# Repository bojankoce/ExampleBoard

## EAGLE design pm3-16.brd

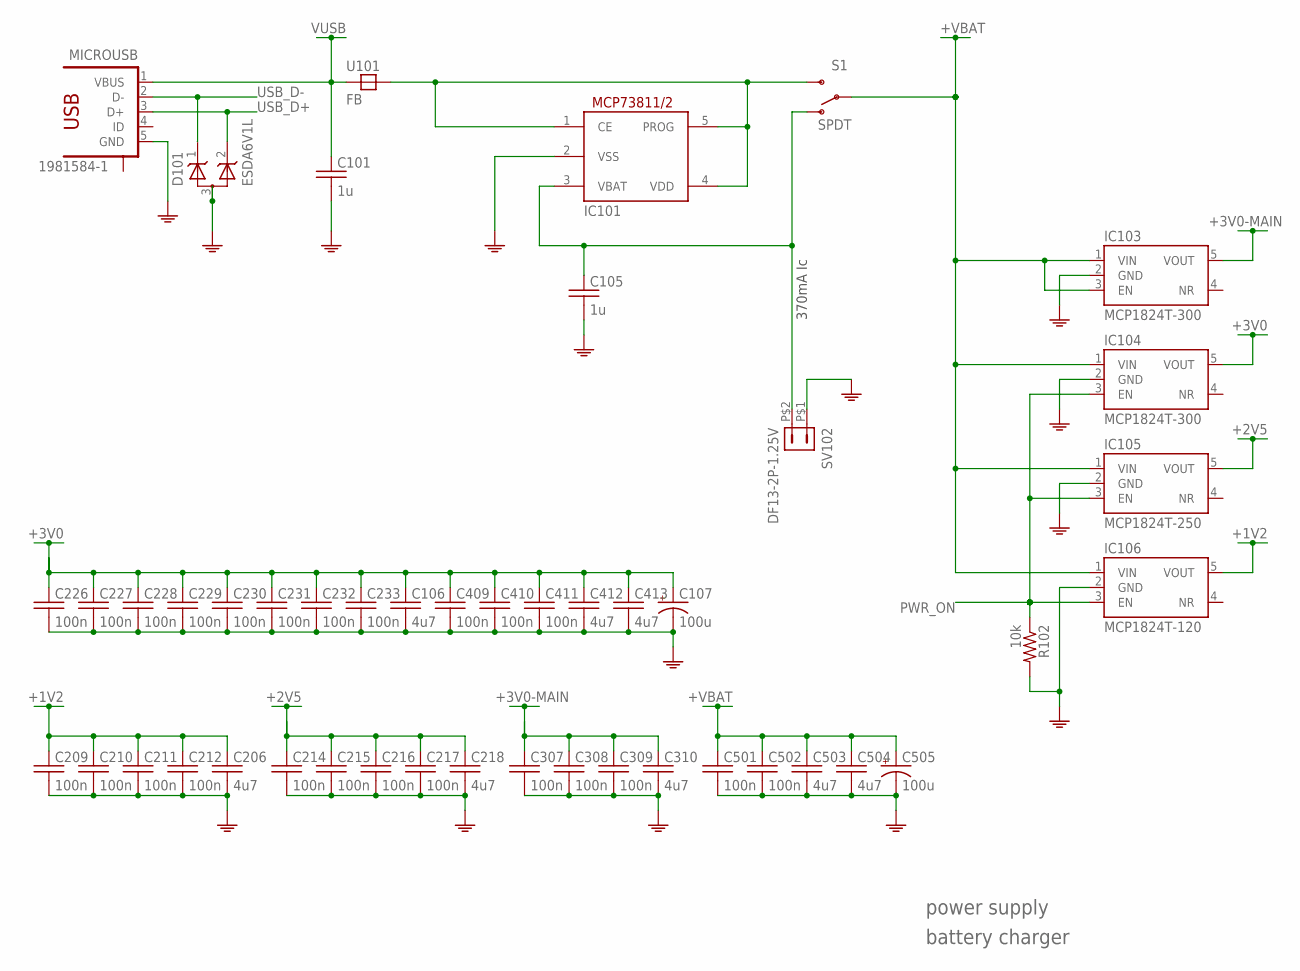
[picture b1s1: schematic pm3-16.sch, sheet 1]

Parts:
C101, C105: 1u; 0603
C106, C206, C218, C310, C412, C413, C503, C504: 4u7; 0603
C107, C505: 100u; 153CLV-0605
C209, C210, C211, C212, C214, C215, C216, C217, C226, C227, C228, C229, C230, C231, C232, C233, C307, C308, C309, C409, C410, C411, C501, C502: 100n; 0603
D101: ESDA6V1L; SOT-23-3
IC101: MCP73811/2; SOT23-5L
IC103, IC104: MCP1824T-300; SOT-23-5
IC105: MCP1824T-250; SOT-23-5
IC106: MCP1824T-120; SOT-23-5
MICROUSB: 1981584-1
R102: 10k; 0603
S1: SPDT; SWITCH-SPDT-SMD
SV102: DF13-2P-1.25V; DF13C-2P-1.25V
U101: FB; 0805

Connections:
+1V2: C206.1, C209.1, C210.1, C211.1, C212.1, IC106.5 (VOUT); also elsewhere on the board
+2V5: C214.1, C215.1, C216.1, C217.1, C218.1, IC105.5 (VOUT); also elsewhere on the board
+3V0: C106.1, C107.+, C226.1, C227.1, C228.1, C229.1, C230.1, C231.1, C232.1, C233.1, C409.1, C410.1, C411.1, C412.1, C413.1, IC104.5 (VOUT); also elsewhere on the board
+3V0-MAIN: C307.1, C308.1, C309.1, C310.1, IC103.5 (VOUT); also elsewhere on the board
+VBAT: C501.1, C502.1, C503.1, C504.1, C505.+, IC103.1 (VIN), IC103.3 (EN), IC104.1 (VIN), IC105.1 (VIN), IC106.1 (VIN), S1.2; also elsewhere on the board
BAT: C105.1, IC101.3 (VBAT), S1.1 (O), SV102.P$2 (2)
GND: C101.2, C105.2, C106.2, C107.-, C206.2, C209.2, C210.2, C211.2, C212.2, C214.2, C215.2, C216.2, C217.2, C218.2, C226.2, C227.2, C228.2, C229.2, C230.2, C231.2, C232.2, C233.2, C307.2, C308.2, C309.2, C310.2, C409.2, C410.2, C411.2, C412.2, C413.2, C501.2, C502.2, C503.2, C504.2, C505.-, D101.3 (AA), IC101.2 (VSS), IC103.2 (GND), IC104.2 (GND), IC105.2 (GND), IC106.2 (GND), MICROUSB.5 (GND), R102.2, SV102.P$1 (1); also elsewhere on the board
unnamed: IC101.1 (CE), IC101.4 (VDD), IC101.5 (PROG), S1.3 (S), U101.2 (B)
PWR_ON: IC104.3 (EN), IC105.3 (EN), IC106.3 (EN), R102.1; also elsewhere on the board
USB_D+: D101.2 (K2), MICROUSB.3 (D+); also elsewhere on the board
USB_D-: D101.1 (K1), MICROUSB.2 (D-); also elsewhere on the board
VUSB: C101.1, MICROUSB.1 (VBUS), U101.1 (A)

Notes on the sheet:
power supply
battery charger
370mA Ic

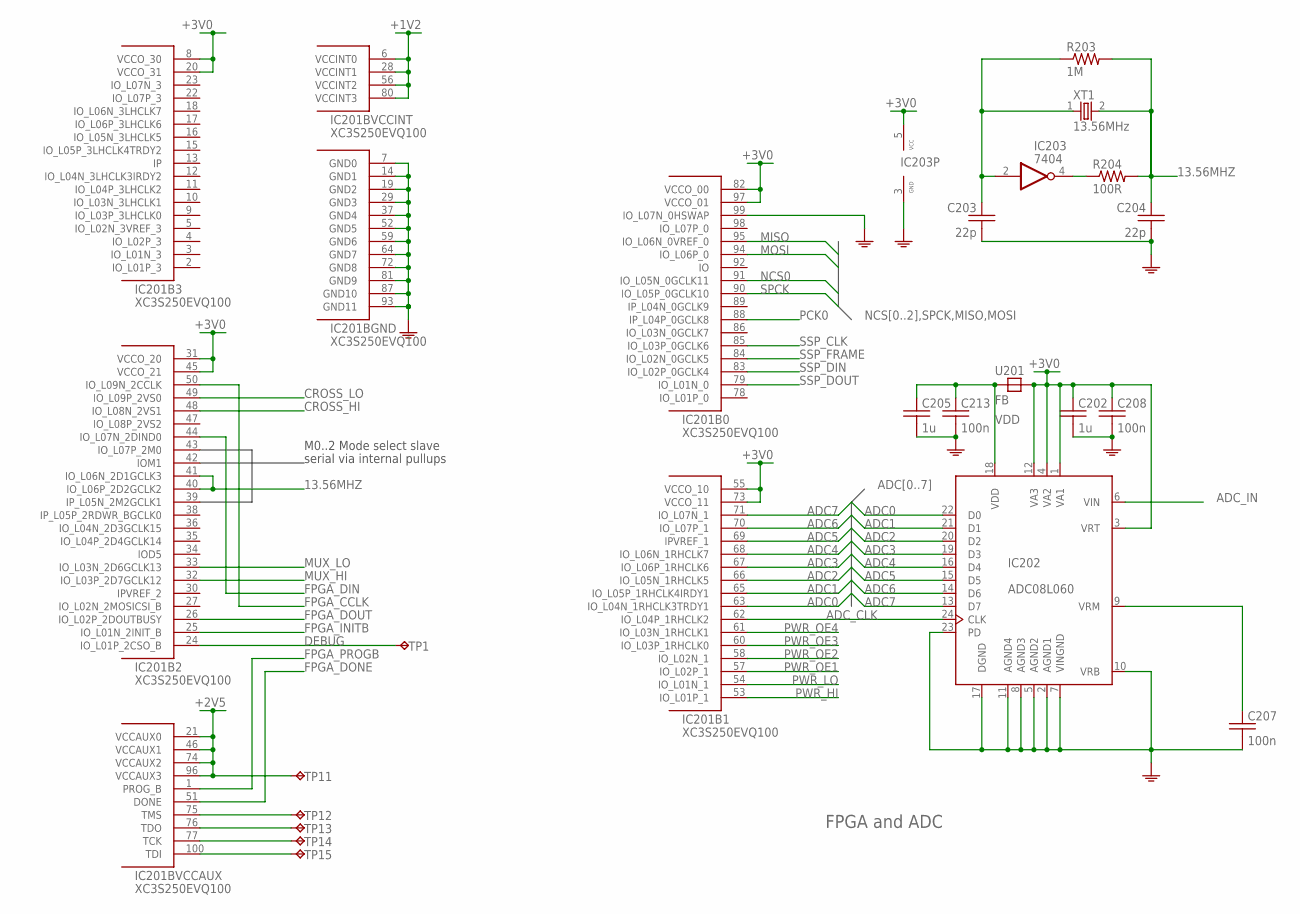
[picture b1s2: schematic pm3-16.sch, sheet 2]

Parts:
C202, C205: 1u; 0603
C203, C204: 22p; 0603
C207, C208, C213: 100n; 0603
IC201: XC3S250EVQ100; VQ100
IC202: ADC08L060; TSSOP24
IC203: 7404; SOT-23-5
R203: 1M; 0603
R204: 100R; 0603
TP1, TP11, TP12, TP13, TP14, TP15: TPTP06SQ; TP06SQ
U201: FB; 0805
XT1: 13.56MHz; 6035

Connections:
13.56MHZ: C204.1, IC201.40 (IO_L06P_2D2GCLK2), IC201.41 (IO_L06N_2D1GCLK3), R203.2, R204.2, XT1.2
+1V2: IC201.6 (VCCINT0), IC201.28 (VCCINT1), IC201.56 (VCCINT2), IC201.80 (VCCINT3); also elsewhere on the board
+2V5: IC201.21 (VCCAUX0), IC201.46 (VCCAUX1), IC201.74 (VCCAUX2), IC201.96 (VCCAUX3), TP11.TP; also elsewhere on the board
+3V0: C202.1, C208.1, IC201.8 (VCCO_30), IC201.20 (VCCO_31), IC201.31 (VCCO_20), IC201.45 (VCCO_21), IC201.55 (VCCO_10), IC201.73 (VCCO_11), IC201.82 (VCCO_00), IC201.97 (VCCO_01), IC202.1 (VA1), IC202.3 (VRT), IC202.4 (VA2), IC202.12 (VA3), IC203.5 (VCC), U201.2 (B); also elsewhere on the board
ADC0: IC201.63 (IO_L04N_1RHCLK3TRDY1), IC202.22 (D0)
ADC1: IC201.65 (IO_L05P_1RHCLK4IRDY1), IC202.21 (D1)
ADC2: IC201.66 (IO_L05N_1RHCLK5), IC202.20 (D2)
ADC3: IC201.67 (IO_L06P_1RHCLK6), IC202.19 (D3)
ADC4: IC201.68 (IO_L06N_1RHCLK7), IC202.16 (D4)
ADC5: IC201.69 (IPVREF_1), IC202.15 (D5)
ADC6: IC201.70 (IO_L07P_1), IC202.14 (D6)
ADC7: IC201.71 (IO_L07N_1), IC202.13 (D7)
ADC_CLK: IC201.62 (IO_L04P_1RHCLK2), IC202.24 (CLK)
ADC_IN: IC202.6 (VIN); also elsewhere on the board
CROSS_HI: IC201.48 (IO_L08N_2VS1); also elsewhere on the board
CROSS_LO: IC201.49 (IO_L09P_2VS0); also elsewhere on the board
DEBUG: IC201.24 (IO_L01P_2CSO_B), TP1.TP
FPGA_CCLK: IC201.50 (IO_L09N_2CCLK); also elsewhere on the board
FPGA_DIN: IC201.44 (IO_L07N_2DIND0); also elsewhere on the board
FPGA_DONE: IC201.51 (DONE); also elsewhere on the board
FPGA_DOUT: IC201.26 (IO_L02P_2DOUTBUSY); also elsewhere on the board
FPGA_INITB: IC201.25 (IO_L01N_2INIT_B); also elsewhere on the board
FPGA_PROGB: IC201.1 (PROG_B); also elsewhere on the board
FPGA_TCK: IC201.77 (TCK), TP14.TP
FPGA_TDI: IC201.100 (TDI), TP15.TP
FPGA_TDO: IC201.76 (TDO), TP13.TP
FPGA_TMS: IC201.75 (TMS), TP12.TP
GND: C202.2, C203.2, C204.2, C205.2, C207.2, C208.2, C213.2, IC201.7 (GND0), IC201.14 (GND1), IC201.19 (GND2), IC201.29 (GND3), IC201.37 (GND4), IC201.52 (GND5), IC201.59 (GND6), IC201.64 (GND7), IC201.72 (GND8), IC201.81 (GND9), IC201.87 (GND10), IC201.93 (GND11), IC201.99 (IO_L07N_0HSWAP), IC202.2 (AGND1), IC202.5 (AGND2), IC202.7 (VINGND), IC202.8 (AGND3), IC202.10 (VRB), IC202.11 (AGND4), IC202.17 (DGND), IC202.23 (PD), IC203.3 (GND); also elsewhere on the board
MISO: IC201.95 (IO_L06N_0VREF_0); also elsewhere on the board
MOSI: IC201.94 (IO_L06P_0); also elsewhere on the board
MUX_HI: IC201.32 (IO_L03P_2D7GCLK12); also elsewhere on the board
MUX_LO: IC201.33 (IO_L03N_2D6GCLK13); also elsewhere on the board
unnamed: C207.1, IC202.9 (VRM)
unnamed: IC203.4 (O), R204.1
unnamed: C203.1, IC203.2 (I), R203.1, XT1.1
NCS0: IC201.91 (IO_L05N_0GCLK11); also elsewhere on the board
PCK0: IC201.88 (IP_L04P_0GCLK8); also elsewhere on the board
PWR_HI: IC201.53 (IO_L01P_1); also elsewhere on the board
PWR_LO: IC201.54 (IO_L01N_1); also elsewhere on the board
PWR_OE1: IC201.57 (IO_L02P_1); also elsewhere on the board
PWR_OE2: IC201.58 (IO_L02N_1); also elsewhere on the board
PWR_OE3: IC201.60 (IO_L03P_1RHCLK0); also elsewhere on the board
PWR_OE4: IC201.61 (IO_L03N_1RHCLK1); also elsewhere on the board
SPCK: IC201.90 (IO_L05P_0GCLK10); also elsewhere on the board
SSP_CLK: IC201.85 (IO_L03P_0GCLK6); also elsewhere on the board
SSP_DIN: IC201.83 (IO_L02P_0GCLK4); also elsewhere on the board
SSP_DOUT: IC201.79 (IO_L01N_0); also elsewhere on the board
SSP_FRAME: IC201.84 (IO_L02N_0GCLK5); also elsewhere on the board
VDD: C205.1, C213.1, IC202.18 (VDD), U201.1 (A)

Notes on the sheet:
FPGA and ADC
M0..2 Mode select slave
serial via internal pullups

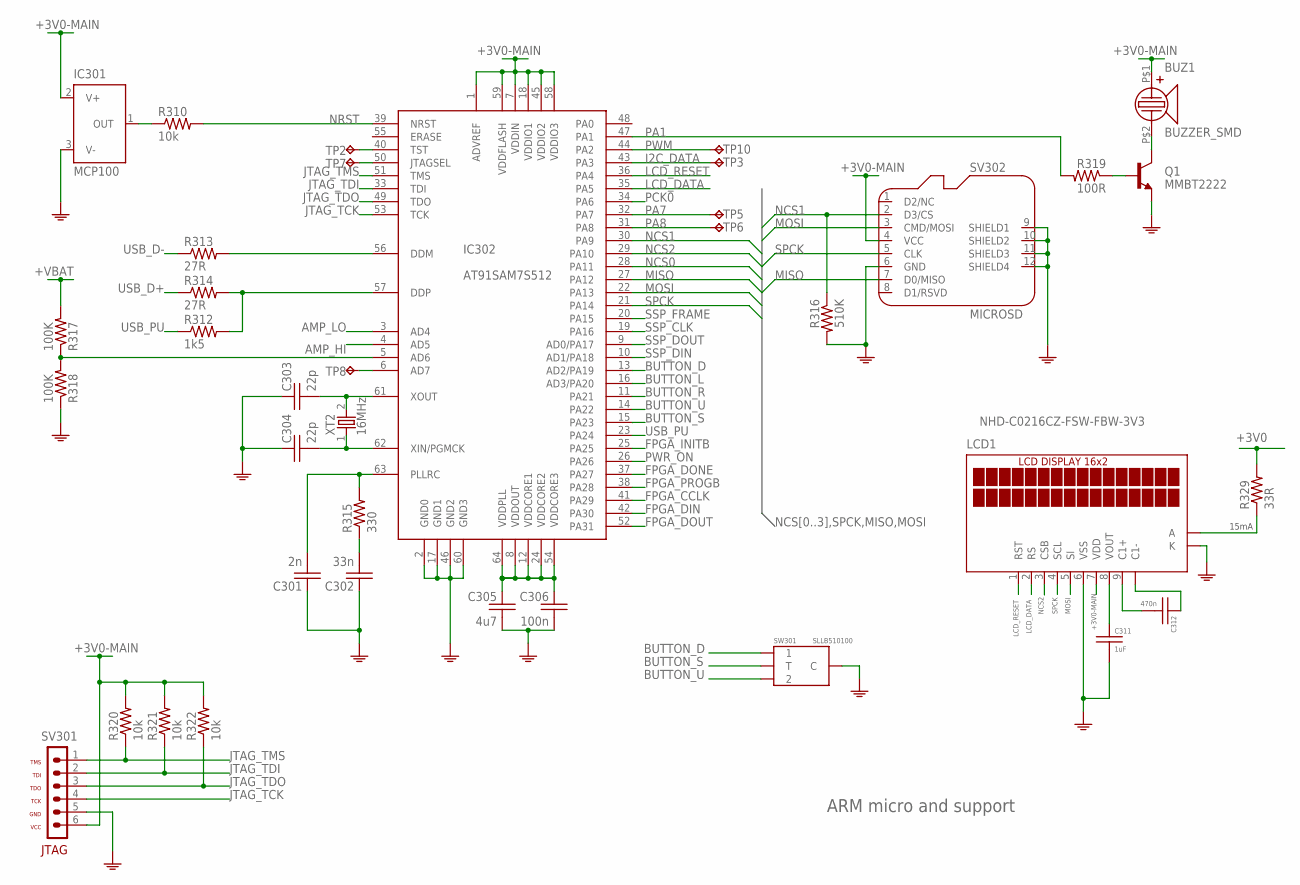
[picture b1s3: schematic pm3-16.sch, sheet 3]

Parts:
BUZ1: BUZZER_SMD
C301: 2n; 0603
C302: 33n; 0603
C303, C304: 22p; 0603
C305: 4u7; 0603
C306: 100n; 0603
C311: 1uF; 0603
C312: 470n; 0603
IC301: MCP100; SOT-23-3
IC302: AT91SAM7S512; LQFP64
LCD1: NHD-C0216CZ-FSW-FBW-3V3
Q1: MMBT2222; SOT-23-3
R310, R320, R321, R322: 10k; 0603
R312: 1k5; 0603
R313, R314: 27R; 0603
R315: 330; 0603
R316: 510K; 0603
R317, R318: 100K; 0603
R319: 100R; 0603
R329: 33R; 0603
SV301: HEADER-1X6
SV302: MICROSD; 3M-MICROSD
SW301: SLLB510100
TP2, TP3, TP5, TP6, TP7, TP8, TP10: TPTP06SQ; TP06SQ
XT2: 16MHz; 6035

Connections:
+3V0: R329.2; also elsewhere on the board
+3V0-MAIN: BUZ1.P$1 (1), IC301.2 (V+), IC302.1 (ADVREF), IC302.7 (VDDIN), IC302.18 (VDDIO1), IC302.45 (VDDIO2), IC302.58 (VDDIO3), IC302.59 (VDDFLASH), LCD1.7 (VDD), R320.2, R321.2, R322.2, SV301.6, SV302.4 (VCC); also elsewhere on the board
+VBAT: R317.2; also elsewhere on the board
AD6: IC302.5 (AD6), R317.1, R318.2
AD7: IC302.6 (AD7), TP8.TP
AMP_HI: IC302.4 (AD5); also elsewhere on the board
AMP_LO: IC302.3 (AD4); also elsewhere on the board
BUTTON_D: IC302.13 (AD2/PA19), SW301.1
BUTTON_L: IC302.16 (AD3/PA20)
BUTTON_R: IC302.11 (PA21)
BUTTON_S: IC302.15 (PA23), SW301.T
BUTTON_U: IC302.14 (PA22), SW301.2
FPGA_CCLK: IC302.41 (PA29); also elsewhere on the board
FPGA_DIN: IC302.42 (PA30); also elsewhere on the board
FPGA_DONE: IC302.37 (PA27); also elsewhere on the board
FPGA_DOUT: IC302.52 (PA31); also elsewhere on the board
FPGA_INITB: IC302.25 (PA25); also elsewhere on the board
FPGA_PROGB: IC302.38 (PA28); also elsewhere on the board
GND: C301.1, C302.1, C303.1, C304.1, C305.2, C306.2, C311.2, IC301.3 (V-), IC302.2 (GND0), IC302.17 (GND1), IC302.46 (GND2), IC302.60 (GND3), LCD1.6 (VSS), LCD1.K, Q1.2 (E), R316.2, R318.1, SV301.5, SV302.6 (GND), SV302.9 (SHIELD1), SV302.10 (SHIELD2), SV302.11 (SHIELD3), SV302.12 (SHIELD4), SW301.C; also elsewhere on the board
I2C_DATA: IC302.43 (PA3), TP3.TP
JTAG_TCK: IC302.53 (TCK), SV301.4
JTAG_TDI: IC302.33 (TDI), R321.1, SV301.2
JTAG_TDO: IC302.49 (TDO), R322.1, SV301.3
JTAG_TMS: IC302.51 (TMS), R320.1, SV301.1
LCD_DATA: IC302.35 (PA5), LCD1.2 (RS)
LCD_RESET: IC302.36 (PA4), LCD1.1 (RST)
MISO: IC302.27 (PA12), SV302.7 (D0/MISO); also elsewhere on the board
MOSI: IC302.22 (PA13), LCD1.5 (SI), SV302.3 (CMD/MOSI); also elsewhere on the board
unnamed: C301.2, IC302.63 (PLLRC), R315.2
unnamed: C302.2, R315.1
unnamed: C303.2, IC302.61 (XOUT), XT2.2
unnamed: C304.2, IC302.62 (XIN/PGMCK), XT2.1
unnamed: LCD1.A, R329.1
unnamed: IC302.40 (TST), TP2.TP
unnamed: IC302.56 (DDM), R313.2
unnamed: IC302.57 (DDP), R312.2, R314.2
unnamed: IC301.1 (OUT), R310.1
unnamed: BUZ1.P$2 (2), Q1.3 (C)
unnamed: Q1.1 (B), R319.1
unnamed: C305.1, C306.1, IC302.8 (VDDOUT), IC302.12 (VDDCORE1), IC302.24 (VDDCORE2), IC302.54 (VDDCORE3), IC302.64 (VDDPLL)
unnamed: IC302.50 (JTAGSEL), TP7.TP
unnamed: C311.1, LCD1.8 (VOUT)
unnamed: C312.2, LCD1.9 (C1+)
unnamed: C312.1, LCD1.10 (C1-)
NCS0: IC302.28 (PA11); also elsewhere on the board
NCS1: IC302.30 (PA9), R316.1, SV302.2 (D3/CS)
NCS2: IC302.29 (PA10), LCD1.3 (CSB)
NRST: IC302.39 (NRST), R310.2
PA1: IC302.47 (PA1), R319.2
PA7: IC302.32 (PA7), TP5.TP
PA8: IC302.31 (PA8), TP6.TP
PCK0: IC302.34 (PA6); also elsewhere on the board
PWM: IC302.44 (PA2), TP10.TP
PWR_ON: IC302.26 (PA26); also elsewhere on the board
SPCK: IC302.21 (PA14), LCD1.4 (SCL), SV302.5 (CLK); also elsewhere on the board
SSP_CLK: IC302.19 (PA16); also elsewhere on the board
SSP_DIN: IC302.10 (AD1/PA18); also elsewhere on the board
SSP_DOUT: IC302.9 (AD0/PA17); also elsewhere on the board
SSP_FRAME: IC302.20 (PA15); also elsewhere on the board
USB_D+: R314.1; also elsewhere on the board
USB_D-: R313.1; also elsewhere on the board
USB_PU: IC302.23 (PA24), R312.1

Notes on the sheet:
ARM micro and support
15mA

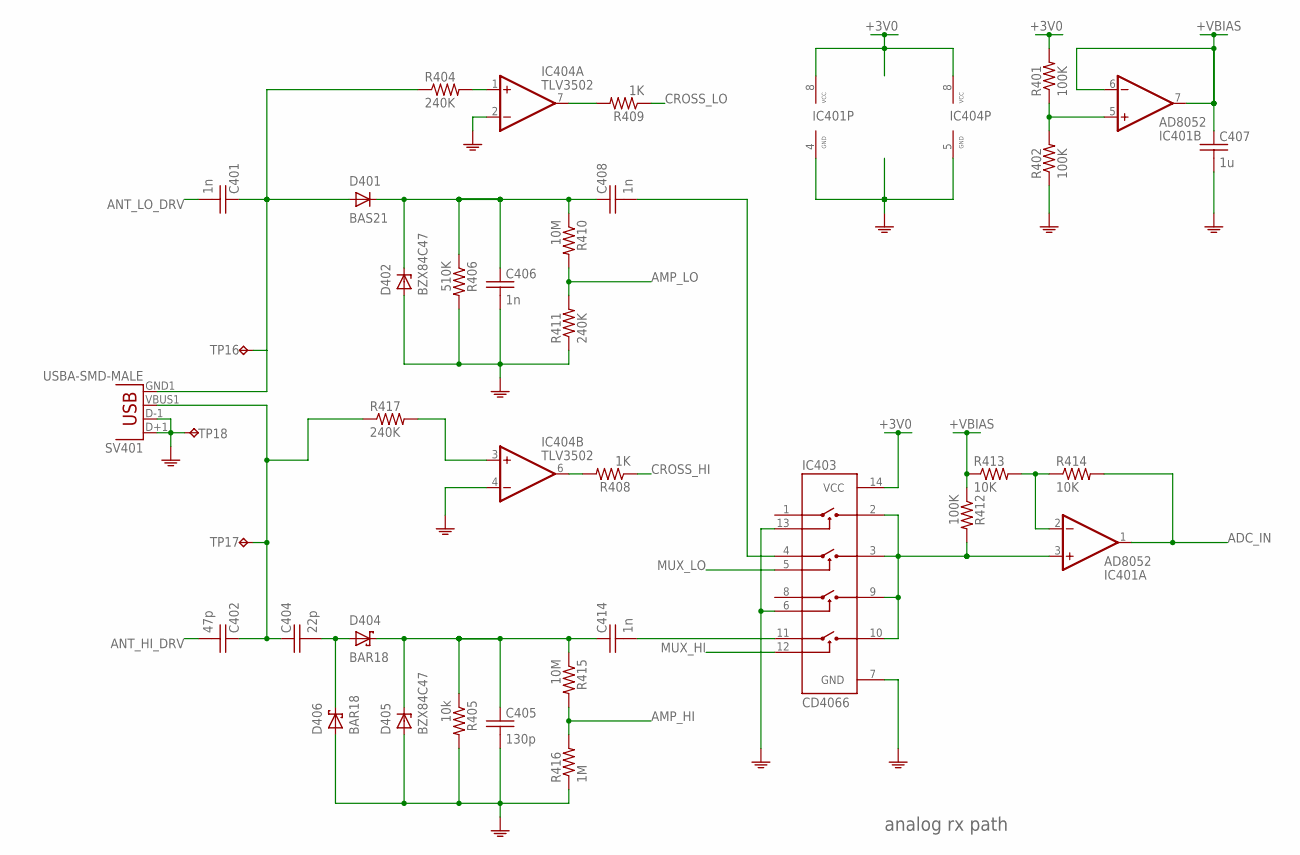
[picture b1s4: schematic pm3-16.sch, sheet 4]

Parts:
C401, C406, C408, C414: 1n; 0603
C402: 47p; 0603
C404: 22p; 0603
C405: 130p; 0603
C407: 1u; 0603
D401: BAS21; SOT-23-3
D402, D405: BZX84C47; SOT-23-3
D404, D406: BAR18; SOT-23-3
IC401: AD8052; MSOP8
IC403: CD4066; TSSOP14
IC404: TLV3502; SOT-23-8
R401, R402, R412: 100K; 0603
R404, R411, R417: 240K; 0603
R405: 10k; 0603
R406: 510K; 0603
R408, R409: 1K; 0603
R410, R415: 10M; 0603
R413, R414: 10K; 0603
R416: 1M; 0603
SV401: USBA-SMD-MALE; USB-A-SMT-MALE
TP16, TP17, TP18: TPTP06SQ; TP06SQ

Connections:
+3V0: IC401.8 (VCC), IC403.14 (VCC), IC404.8 (VCC), R401.2; also elsewhere on the board
+VBIAS: C407.1, IC401.6 (-IN), IC401.7 (OUT), R412.1, R413.1
ADCDR_HI: C405.1, C414.1, D404.3 (C), D405.3 (C), R405.1, R415.1
ADCDR_LO: C406.1, C408.1, D401.3 (C), D402.3 (C), R406.1, R410.1
ADC_IN: IC401.1 (OUT), R414.2; also elsewhere on the board
AMP_HI: R415.2, R416.2; also elsewhere on the board
AMP_LO: R410.2, R411.2; also elsewhere on the board
ANT_HI_DRV: C402.2; also elsewhere on the board
ANT_LO_DRV: C401.2; also elsewhere on the board
CROSS_HI: R408.1; also elsewhere on the board
CROSS_LO: R409.1; also elsewhere on the board
GND: C405.2, C406.2, C407.2, D402.1 (A), D405.1 (A), D406.1 (A), IC401.4 (GND), IC403.6 (C3), IC403.7 (GND), IC403.13 (C1), IC404.2 (-IN), IC404.4 (-IN), IC404.5 (GND), R402.1, R405.2, R406.2, R411.1, R416.1, SV401.D+1 (D+), SV401.D-1 (D-), TP18.TP; also elsewhere on the board
MUX_HI: IC403.12 (C4); also elsewhere on the board
MUX_LO: IC403.5 (C2); also elsewhere on the board
unnamed: IC401.5 (+IN), R401.1, R402.2
unnamed: C414.2, IC403.11 (A4)
unnamed: C401.1, D401.1 (A), R404.1, SV401.GND1 (GND), TP16.TP
unnamed: C404.2, D404.1 (A), D406.3 (C)
unnamed: IC404.1 (+IN), R404.2
unnamed: IC404.7 (OUT), R409.2
unnamed: IC401.3 (+IN), IC403.2 (B1), IC403.3 (B2), IC403.9 (B3), IC403.10 (B4), R412.2
unnamed: IC404.6 (OUT), R408.2
unnamed: IC404.3 (+IN), R417.2
unnamed: C408.2, IC403.4 (A2)
unnamed: C402.1, C404.1, R417.1, SV401.VBUS1 (VBUS), TP17.TP
unnamed: IC401.2 (-IN), R413.2, R414.1

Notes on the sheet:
analog rx path

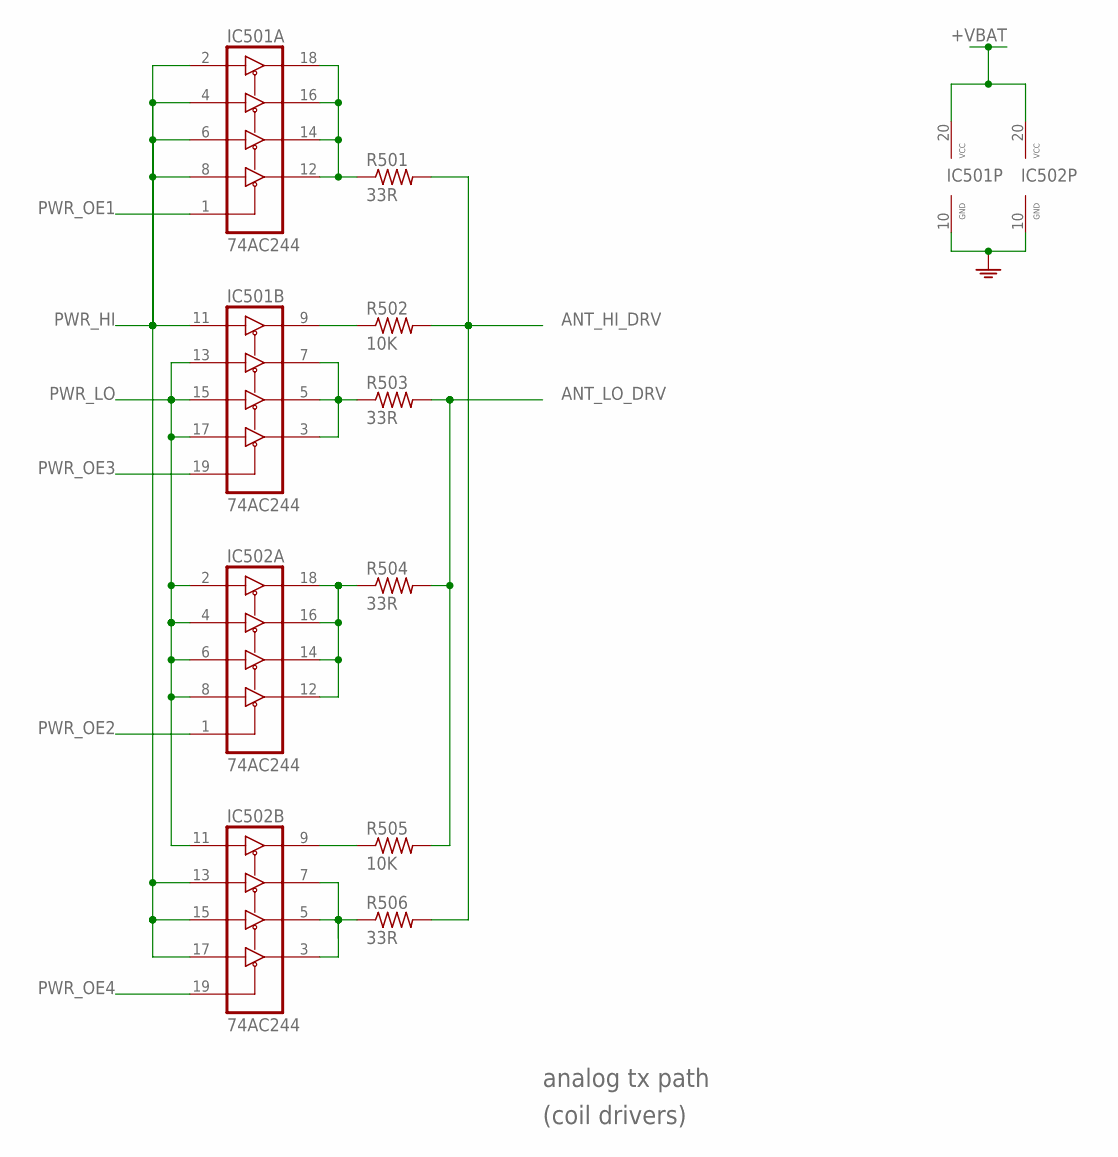
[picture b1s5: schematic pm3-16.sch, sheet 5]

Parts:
IC501, IC502: 74AC244; TSSOP20
R501, R503, R504, R506: 33R; 0603
R502, R505: 10K; 0603

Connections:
+VBAT: IC501.20 (VCC), IC502.20 (VCC); also elsewhere on the board
ANT_HI_DRV: R501.2, R502.2, R506.2; also elsewhere on the board
ANT_LO_DRV: R503.2, R504.2, R505.2; also elsewhere on the board
GND: IC501.10 (GND), IC502.10 (GND); also elsewhere on the board
unnamed: IC501.12 (Y4), IC501.14 (Y3), IC501.16 (Y2), IC501.18 (Y1), R501.1
unnamed: IC502.12 (Y4), IC502.14 (Y3), IC502.16 (Y2), IC502.18 (Y1), R504.1
unnamed: IC501.3 (Y4), IC501.5 (Y3), IC501.7 (Y2), R503.1
unnamed: IC502.3 (Y4), IC502.5 (Y3), IC502.7 (Y2), R506.1
unnamed: IC501.9 (Y1), R502.1
unnamed: IC502.9 (Y1), R505.1
PWR_HI: IC501.2 (A1), IC501.4 (A2), IC501.6 (A3), IC501.8 (A4), IC501.11 (A1), IC502.13 (A2), IC502.15 (A3), IC502.17 (A4); also elsewhere on the board
PWR_LO: IC501.13 (A2), IC501.15 (A3), IC501.17 (A4), IC502.2 (A1), IC502.4 (A2), IC502.6 (A3), IC502.8 (A4), IC502.11 (A1); also elsewhere on the board
PWR_OE1: IC501.1 (G); also elsewhere on the board
PWR_OE2: IC502.1 (G); also elsewhere on the board
PWR_OE3: IC501.19 (G); also elsewhere on the board
PWR_OE4: IC502.19 (G); also elsewhere on the board

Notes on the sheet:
analog tx path
(coil drivers)

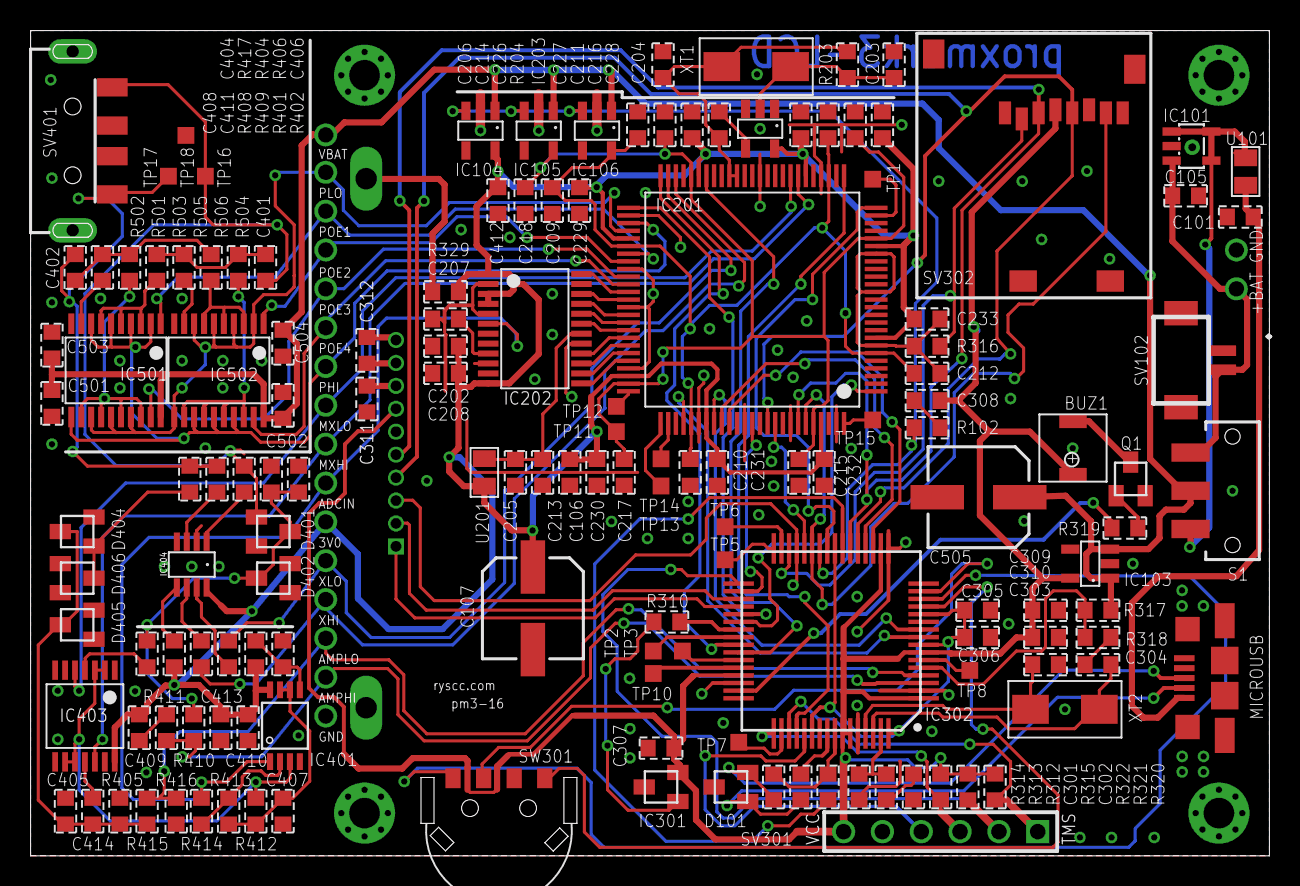
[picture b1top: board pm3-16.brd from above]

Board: 2 copper layers, 81.0 x 53.9 mm, 147 parts (1 on the bottom side), 118 nets.

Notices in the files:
parts and their libraries:
con-usb: Copyright (C) 2008, Bob Starr
SparkFun-Connectors: Licensing: Creative Commons ShareAlike 4.0 International - https://creativecommons.org/licenses/by-sa/4.0
